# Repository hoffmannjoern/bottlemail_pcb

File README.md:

bottlemail_pcb
==============

PCB layout and schematics for Bottl(e)mail

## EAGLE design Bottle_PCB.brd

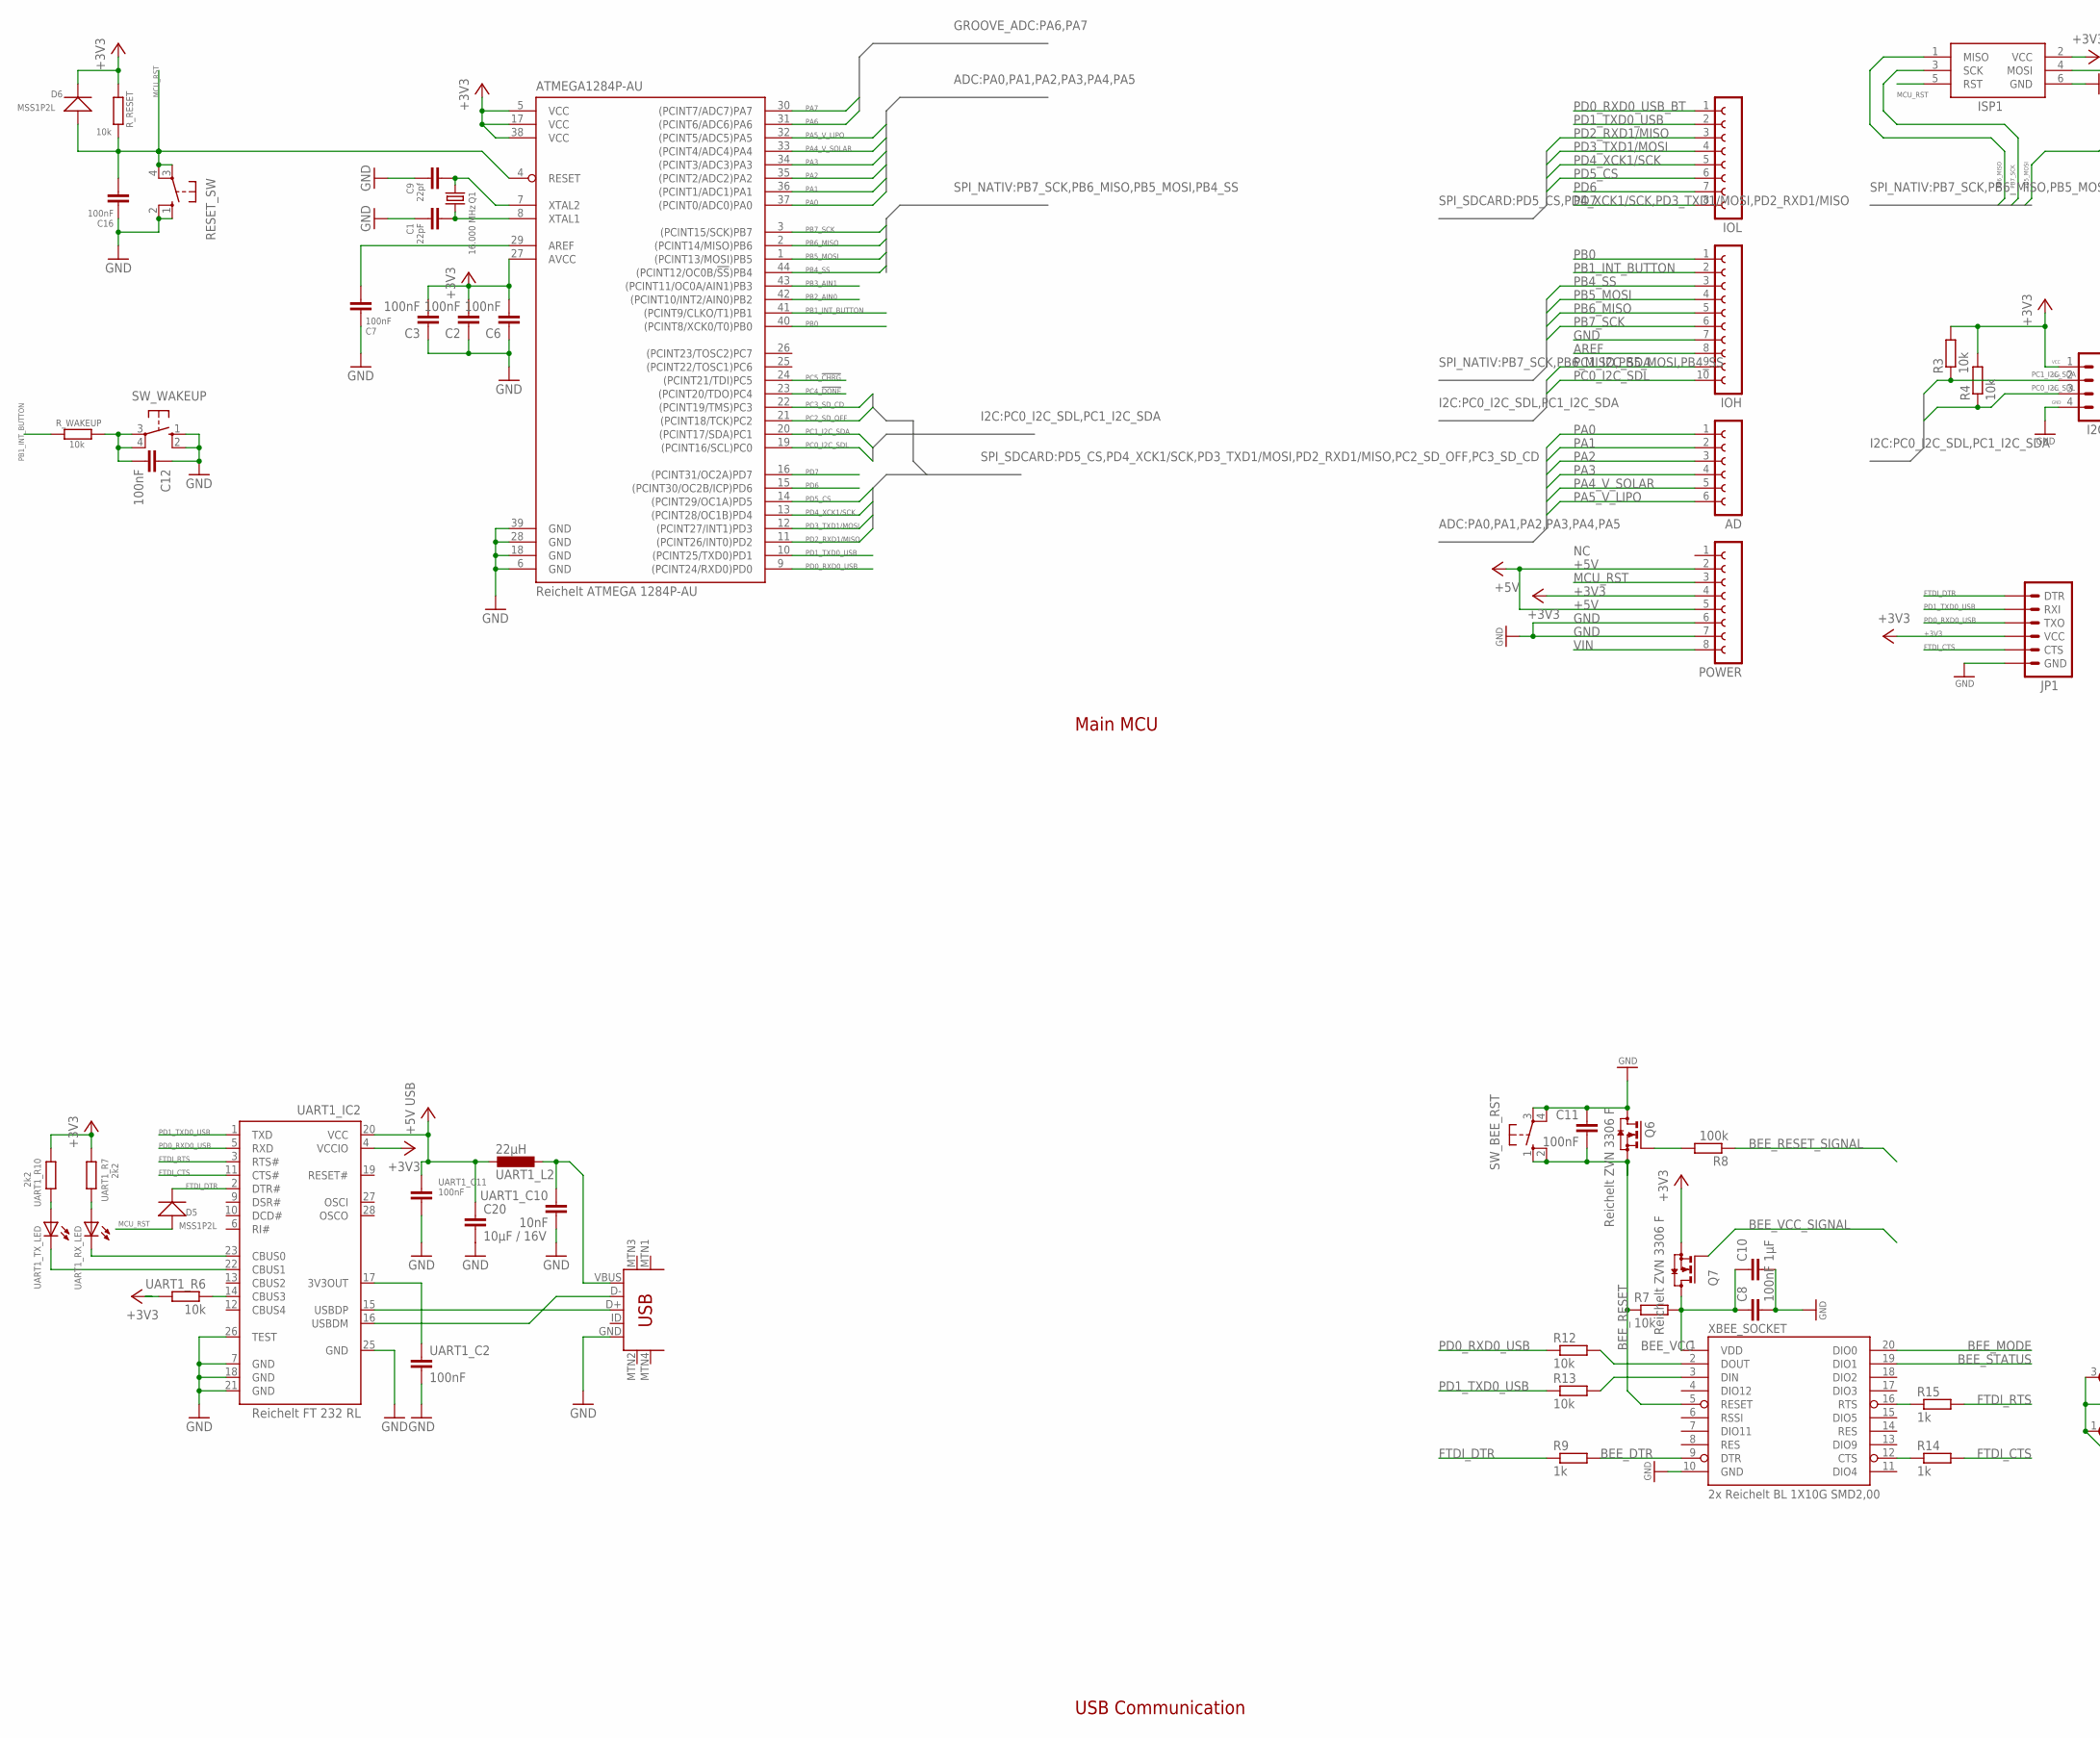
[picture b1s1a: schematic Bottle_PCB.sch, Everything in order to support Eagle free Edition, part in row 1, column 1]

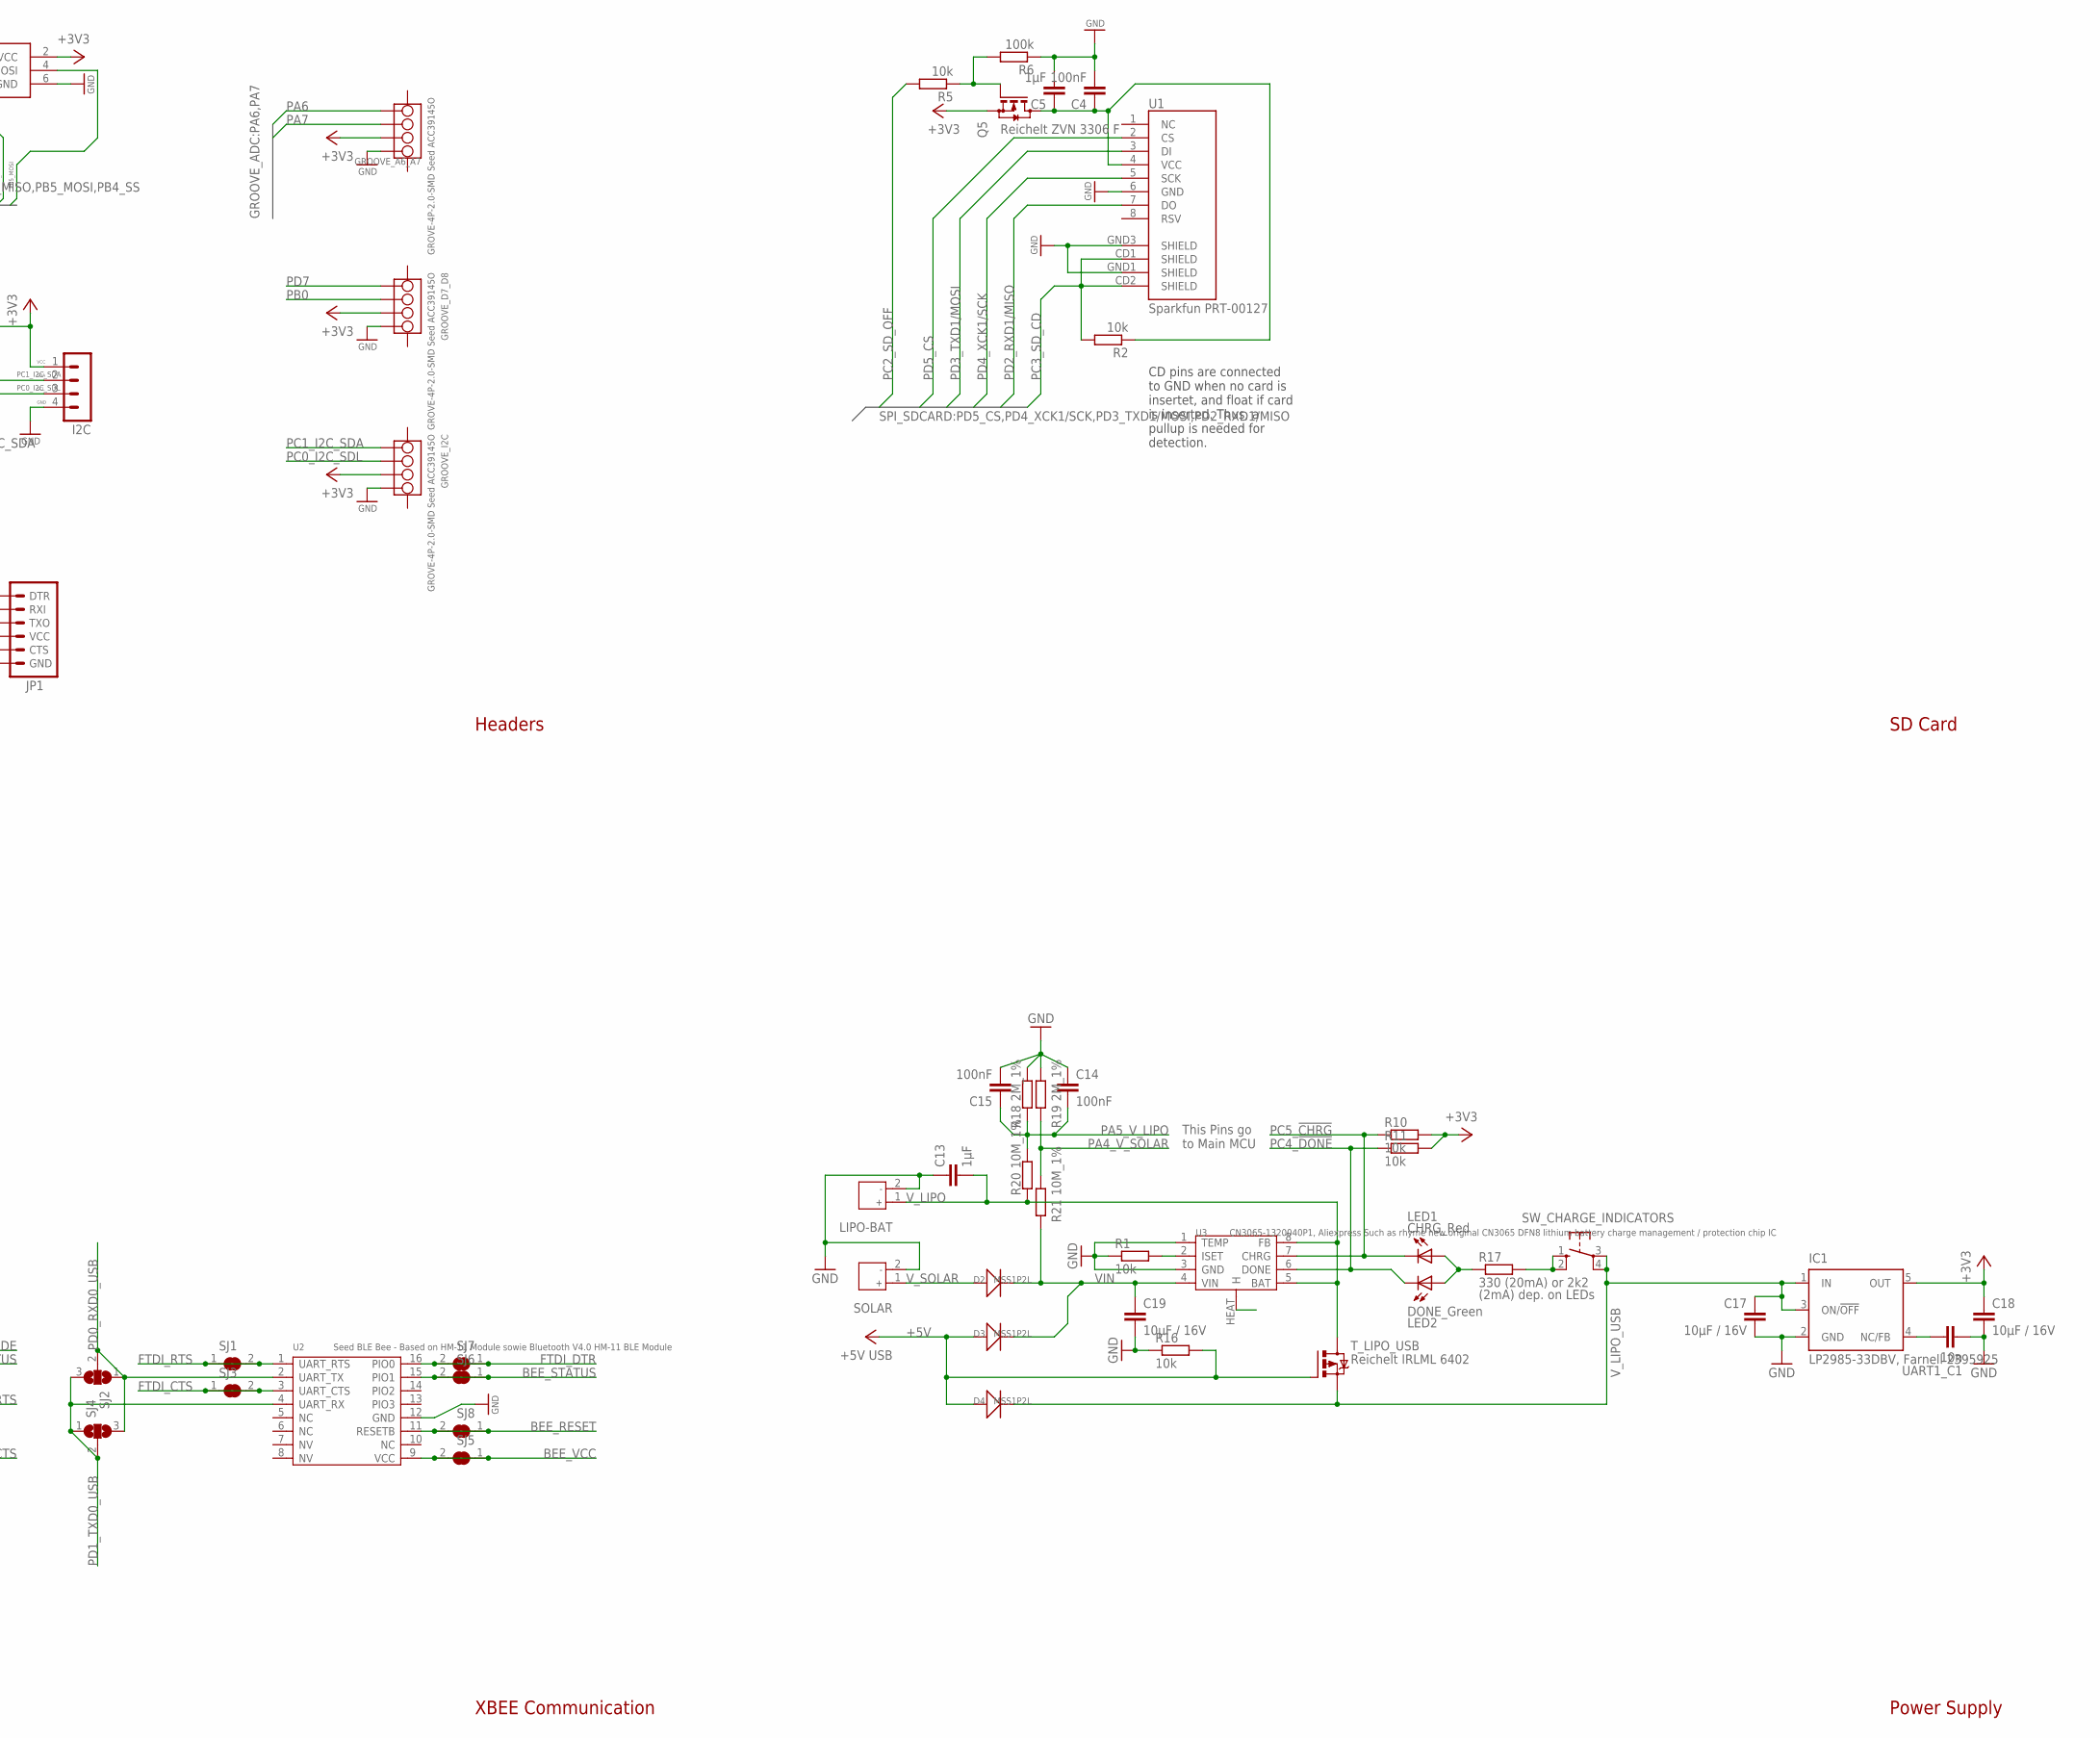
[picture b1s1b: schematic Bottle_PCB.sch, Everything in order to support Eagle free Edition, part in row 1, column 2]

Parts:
AD: FE06-1; FE06
ATMEGA1284P-AU: Reichelt ATMEGA 1284P-AU; TQFP44
C1: 22pF; C0603-ROUND
C2, C3, C4, C6, C7, C8, C11, C12, C14, C15, C16: 100nF; C0603-ROUND
C5, C10, C13: 1µF; C1210
C9: 22pf; C0603-ROUND
C17, C18, C19, C20: 10µF / 16V; C0805
D2, D3, D4, D5, D6: MSS1P2L; D1005
GROOVE_A6_A7: GROVE-4P-2.0-SMD Seed ACC39145O; 4P-SMD-2.0
GROOVE_D7_D8: GROVE-4P-2.0-SMD Seed ACC39145O; 4P-SMD-2.0
GROOVE_I2C: GROVE-4P-2.0-SMD Seed ACC39145O; 4P-SMD-2.0
I2C: MA04-1
IC1: LP2985-33DBV, Farnell 2395925; SOT23-DBV
IOH: FE10-1; FE10
IOL: FE08-1; FE08
ISP1: Reichelt WSL 6G; AVRISP
JP1: ARDUINO_SERIAL_PROGRAMPTH; 1X06
LED1: CHRG_Red; CHIPLED_0603
LED2: DONE_Green; CHIPLED_0603
LIPO-BAT: JACK-JST-2P-PW2.0; JST-2.0
POWER: FE08-1; FE08
Q1: 16.000 MHz; HC49U-V
Q5, Q6, Q7: Reichelt ZVN 3306 F; SOT23
R1, R2, R3, R4, R5, R7, R10, R11, R12, R13, R16: 10k; R0603-ROUND
R6, R8: 100k; R0603-ROUND
R9, R14, R15: 1k; R0603-ROUND
R17: 330 (20mA) or 2k2; R0603-ROUND
R18, R19: 2M_1%; R0603-ROUND
R20, R21: 10M_1%; R0603-ROUND
RESET_SW: 10-XX; B3F-10XX
R_RESET: 10k; R0603-ROUND
R_WAKEUP: 10k; R0603-ROUND
SJ1, SJ3, SJ5, SJ6, SJ7, SJ8: SJ
SJ2, SJ4: SJ2W; SJ_2
SOLAR: JACK-JST-2P-PW2.0; JST-2.0
SW_BEE_RST: 10-XX; B3F-10XX
SW_CHARGE_INDICATORS: 10-XX; B3F-10XX
SW_WAKEUP: 10-XX; B3F-10XX
T_LIPO_USB: Reichelt IRLML 6402; SOT23
U1: Sparkfun PRT-00127; MICRO-SD-SOCKET-PP
U2: Seed BLE Bee - Based on HM-11 Module sowie Blueto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; 16P-18.5X13.5X0.8
U3: CN3065-1320040P1, Aliexpress Such as rhyme new or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; DFN8
UART1_C1: 10n; C0603-ROUND
UART1_C2, UART1_C11: 100nF; C0603-ROUND
UART1_C10: 10nF; C0603-ROUND
UART1_IC2: Reichelt FT 232 RL; SSOP28
UART1_L2: 22µH; L1812
UART1_R6: 10k; R0603-ROUND
UART1_R7, UART1_R10: 2k2; R0603-ROUND
UART1_RX_LED, UART1_TX_LED: LEDCHIPLED_0603; CHIPLED_0603
USB_CONNECTOR: USB-MINIB-5PIN Sparkfun PRT-00587; USB-MINIB
XBEE_SOCKET: 2x Reichelt BL 1X10G SMD2,00; XBEE-SMD

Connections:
+3V3: ATMEGA1284P-AU.5 (VCC), ATMEGA1284P-AU.17 (VCC), ATMEGA1284P-AU.27 (AVCC), ATMEGA1284P-AU.38 (VCC), C2.2, C3.2, C6.2, C18.1, D6.-, GROOVE_A6_A7.2, GROOVE_D7_D8.2, GROOVE_I2C.2, I2C.1, IC1.5 (OUT), ISP1.2 (VCC), JP1.VCC, POWER.4, Q5.2 (S), Q7.2 (S), R3.2, R4.2, R10.2, R11.2, R_RESET.2, UART1_IC2.4 (VCCIO), UART1_R6.2, UART1_R7.1, UART1_R10.1
+5V: C20.1, D3.+, D4.+, POWER.2, POWER.5, R16.2, T_LIPO_USB.1 (G), UART1_C11.1, UART1_IC2.20 (VCC), UART1_L2.2
AREF: ATMEGA1284P-AU.29 (AREF), C7.2, IOH.8
BEE_DTR: R9.2, XBEE_SOCKET.9 (DTR)
BEE_MODE: XBEE_SOCKET.20 (DIO0)
BEE_RESET: C11.2, Q6.2 (S), R7.1, SJ8.1, SJ8.2, SW_BEE_RST.1 (S), SW_BEE_RST.2 (S1), U2.11 (RESETB), XBEE_SOCKET.5 (RESET)
BEE_RESET_SIGNAL: R8.1
BEE_STATUS: SJ6.1, SJ6.2, U2.15 (PIO1), XBEE_SOCKET.19 (DIO1)
BEE_VCC: C8.1, C10.1, Q7.3 (D), R7.2, SJ5.1, SJ5.2, U2.9 (VCC), XBEE_SOCKET.1 (VDD)
BEE_VCC_SIGNAL: Q7.1 (G)
FTDI_CTS: JP1.CTS, R14.2, SJ3.1, SJ3.2, U2.3 (UART_CTS), UART1_IC2.11 (CTS#)
FTDI_DTR: D5.-, JP1.DTR, R9.1, SJ7.1, SJ7.2, U2.16 (PIO0), UART1_IC2.2 (DTR#)
FTDI_RTS: R15.2, SJ1.1, SJ1.2, U2.1 (UART_RTS), UART1_IC2.3 (RTS#)
GND: ATMEGA1284P-AU.6 (GND), ATMEGA1284P-AU.18 (GND), ATMEGA1284P-AU.28 (GND), ATMEGA1284P-AU.39 (GND), C1.1, C2.1, C3.1, C4.2, C5.2, C6.1, C7.1, C8.2, C9.1, C10.2, C11.1, C12.1, C13.1, C14.1, C15.2, C16.1, C17.2, C18.2, C19.2, C20.2, GROOVE_A6_A7.1, GROOVE_D7_D8.1, GROOVE_I2C.1, I2C.4, IC1.2 (GND), IOH.7, ISP1.6 (GND), JP1.GND, LIPO-BAT.2, POWER.6, POWER.7, Q6.3 (D), R1.1, R6.1, R16.1, R18.2, R19.2, RESET_SW.1 (S), RESET_SW.2 (S1), SOLAR.2, SW_BEE_RST.3, SW_BEE_RST.4 (P1), SW_WAKEUP.1 (S), SW_WAKEUP.2 (S1), U1.6 (GND), U1.GND1 (SHIELD), U1.GND3 (SHIELD), U2.12 (GND), U3.1 (TEMP), U3.3 (GND), UART1_C1.2, UART1_C2.2, UART1_C10.2, UART1_C11.2, UART1_IC2.7 (GND), UART1_IC2.18 (GND), UART1_IC2.21 (GND), UART1_IC2.25 (GND), UART1_IC2.26 (TEST), USB_CONNECTOR.GND, XBEE_SOCKET.10 (GND)
MCU_RST: ATMEGA1284P-AU.4 (RESET), C16.2, D5.+, D6.+, ISP1.5 (RST), POWER.3, RESET_SW.3, RESET_SW.4 (P1), R_RESET.1
unnamed: UART1_R10.2, UART1_TX_LED.A
unnamed: UART1_C2.1, UART1_IC2.17 (3V3OUT)
unnamed: IC1.4 (NC/FB), UART1_C1.1
unnamed: UART1_IC2.16 (USBDM), USB_CONNECTOR.D-
unnamed: R14.1, XBEE_SOCKET.12 (CTS)
unnamed: R15.1, XBEE_SOCKET.16 (RTS)
unnamed: R12.2, XBEE_SOCKET.2 (DOUT)
unnamed: UART1_R7.2, UART1_RX_LED.A
unnamed: UART1_IC2.15 (USBDP), USB_CONNECTOR.D+
unnamed: UART1_IC2.14 (CBUS3), UART1_R6.1
unnamed: UART1_C10.1, UART1_L2.1, USB_CONNECTOR.VBUS
unnamed: UART1_IC2.23 (CBUS0), UART1_RX_LED.C
unnamed: UART1_IC2.22 (CBUS1), UART1_TX_LED.C
unnamed: R13.2, XBEE_SOCKET.3 (DIN)
unnamed: C12.2, R_WAKEUP.1, SW_WAKEUP.3, SW_WAKEUP.4 (P1)
unnamed: LED1.A, LED2.A, R17.1
unnamed: R17.2, SW_CHARGE_INDICATORS.1 (S), SW_CHARGE_INDICATORS.2 (S1)
unnamed: R1.2, U3.2 (ISET)
unnamed: C4.1, C5.1, Q5.3 (D), R2.1, U1.4 (VCC)
unnamed: Q5.1 (G), R5.1, R6.2
unnamed: Q6.1 (G), R8.2
PA0: AD.1, ATMEGA1284P-AU.37 ((PCINT0/ADC0)PA0)
PA1: AD.2, ATMEGA1284P-AU.36 ((PCINT1/ADC1)PA1)
PA2: AD.3, ATMEGA1284P-AU.35 ((PCINT2/ADC2)PA2)
PA3: AD.4, ATMEGA1284P-AU.34 ((PCINT3/ADC3)PA3)
PA4_V_SOLAR: AD.5, ATMEGA1284P-AU.33 ((PCINT4/ADC4)PA4), R19.1, R21.2
PA5_V_LIPO: AD.6, ATMEGA1284P-AU.32 ((PCINT5/ADC5)PA5), C14.2, C15.1, R18.1, R20.2
PA6: ATMEGA1284P-AU.31 ((PCINT6/ADC6)PA6), GROOVE_A6_A7.4
PA7: ATMEGA1284P-AU.30 ((PCINT7/ADC7)PA7), GROOVE_A6_A7.3
PB0: ATMEGA1284P-AU.40 ((PCINT8/XCK0/T0)PB0), GROOVE_D7_D8.3, IOH.1
PB1_INT_BUTTON: ATMEGA1284P-AU.41 ((PCINT9/CLKO/T1)PB1), IOH.2
PB2_AIN0: ATMEGA1284P-AU.42 ((PCINT10/INT2/AIN0)PB2)
PB3_AIN1: ATMEGA1284P-AU.43 ((PCINT11/OC0A/AIN1)PB3)
PB4_SS: ATMEGA1284P-AU.44 ((PCINT12/OC0B/!SS!)PB4), IOH.3
PB5_MOSI: ATMEGA1284P-AU.1 ((PCINT13/MOSI)PB5), IOH.4, ISP1.4 (MOSI)
PB6_MISO: ATMEGA1284P-AU.2 ((PCINT14/MISO)PB6), IOH.5, ISP1.1 (MISO)
PB7_SCK: ATMEGA1284P-AU.3 ((PCINT15/SCK)PB7), IOH.6, ISP1.3 (SCK)
PC0_I2C_SDL: ATMEGA1284P-AU.19 ((PCINT16/SCL)PC0), GROOVE_I2C.3, I2C.3, IOH.10, R4.1
PC1_I2C_SDA: ATMEGA1284P-AU.20 ((PCINT17/SDA)PC1), GROOVE_I2C.4, I2C.2, IOH.9, R3.1
PC2_SD_OFF: ATMEGA1284P-AU.21 ((PCINT18/TCK)PC2), R5.2
PC3_SD_CD: ATMEGA1284P-AU.22 ((PCINT19/TMS)PC3), R2.2, U1.CD1 (SHIELD), U1.CD2 (SHIELD)
PC4_!DONE: ATMEGA1284P-AU.23 ((PCINT20/TDO)PC4), LED2.C, R11.1, U3.6 (DONE)
PC5_!CHRG: ATMEGA1284P-AU.24 ((PCINT21/TDI)PC5), LED1.C, R10.1, U3.7 (CHRG)
PD0_RXD0_USB: ATMEGA1284P-AU.9 ((PCINT24/RXD0)PD0), JP1.TXO, R12.1, SJ2.1, SJ2.2, SJ4.3, U2.2 (UART_TX), UART1_IC2.5 (RXD)
PD0_RXD0_USB_BT: IOL.1
PD1_TXD0_USB: ATMEGA1284P-AU.10 ((PCINT25/TXD0)PD1), IOL.2, JP1.RXI, R13.1, SJ2.3, SJ4.1, SJ4.2, U2.4 (UART_RX), UART1_IC2.1 (TXD)
PD2_RXD1/MISO: ATMEGA1284P-AU.11 ((PCINT26/INT0)PD2), IOL.3, U1.7 (DO)
PD3_TXD1/MOSI: ATMEGA1284P-AU.12 ((PCINT27/INT1)PD3), IOL.4, U1.3 (DI)
PD4_XCK1/SCK: ATMEGA1284P-AU.13 ((PCINT28/OC1B)PD4), IOL.5, U1.5 (SCK)
PD5_CS: ATMEGA1284P-AU.14 ((PCINT29/OC1A)PD5), IOL.6, U1.2 (CS)
PD6: ATMEGA1284P-AU.15 ((PCINT30/OC2B/ICP)PD6), IOL.7
PD7: ATMEGA1284P-AU.16 ((PCINT31/OC2A)PD7), GROOVE_D7_D8.4, IOL.8
VIN: C19.1, D2.-, D3.-, POWER.8, R21.1, U3.4 (VIN)
V_LIPO: C13.2, LIPO-BAT.1, R20.1, T_LIPO_USB.2 (D), U3.5 (BAT), U3.8 (FB)
V_LIPO_USB: C17.1, D4.-, IC1.1 (IN), IC1.3 (ON/!OFF), SW_CHARGE_INDICATORS.3, SW_CHARGE_INDICATORS.4 (P1), T_LIPO_USB.3 (S)
V_SOLAR: D2.+, SOLAR.1
XTAL1: ATMEGA1284P-AU.8 (XTAL1), C1.2, Q1.1
XTAL2: ATMEGA1284P-AU.7 (XTAL2), C9.2, Q1.2

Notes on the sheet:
VCC
SDA
SCL
GND
Main MCU
Headers
XBEE Communication
USB Communication
SD Card
Power Supply
CD pins are connected to GND when no card is insertet, and float if card is inserted. Thus, a pullup is needed for detection.
(2mA) dep. on LEDs
This Pins go to Main MCU

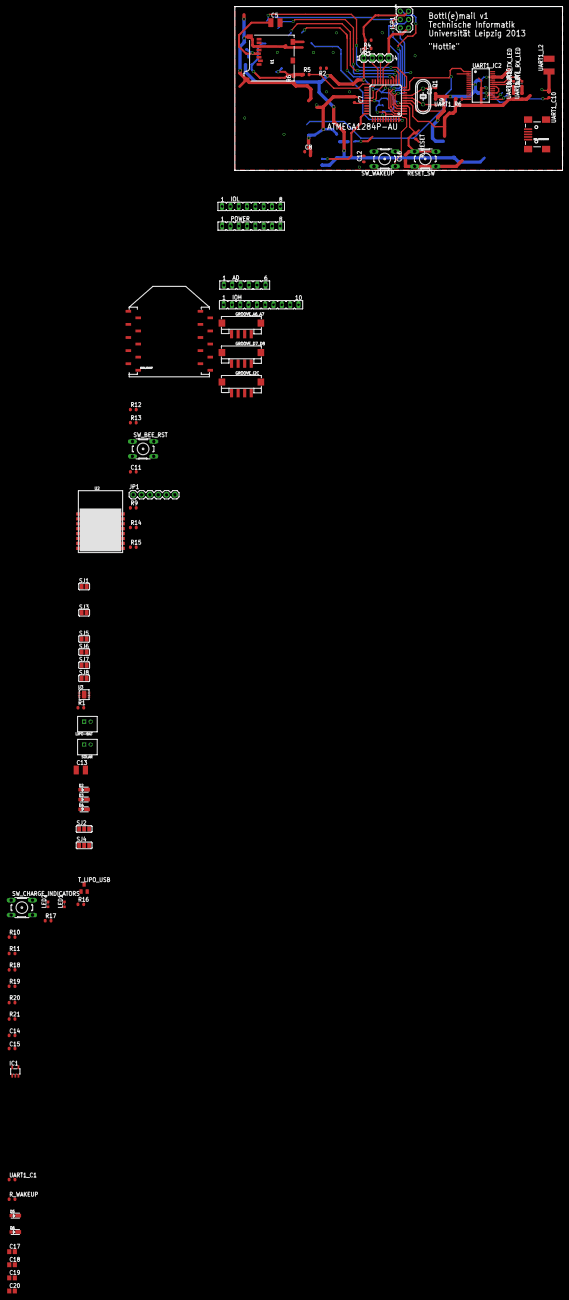
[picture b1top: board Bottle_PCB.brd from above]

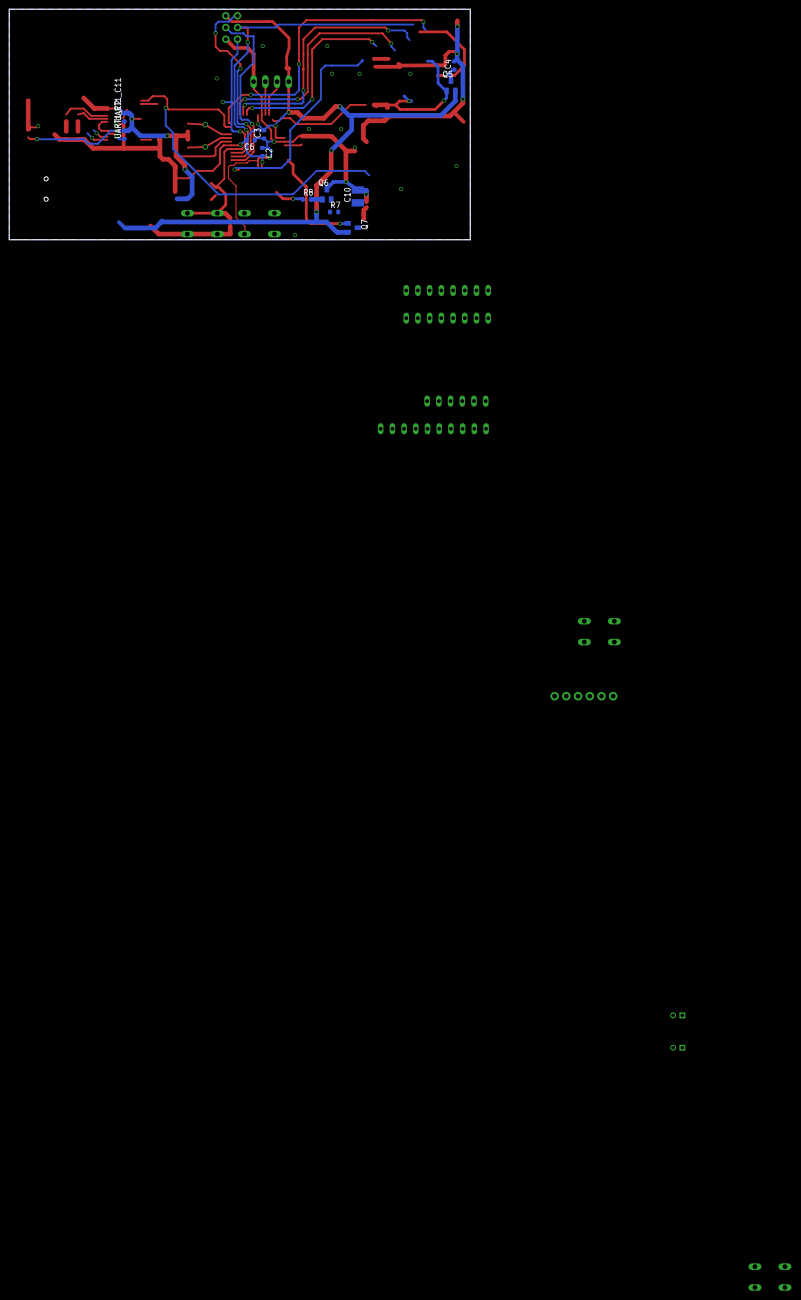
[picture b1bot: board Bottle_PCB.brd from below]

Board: 2 copper layers, 100.0 x 50.0 mm, 97 parts (12 on the bottom side), 67 nets.

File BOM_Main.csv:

Qty,Value,Device,Package,Parts,Description,MF,MPN,OC_FARNELL,OC_NEWARK,PROD_ID
4,,10-XX,B3F-10XX,"RESET_SW, SW_BEE_RST, SW_CHARGE_INDICATORS, SW_WAKEUP",OMRON SWITCH,,B3F-1000,176432,36M3542,
1,,ARDUINO_SERIAL_PROGRAMPTH,1X06,JP1,FTDI connector footprints,,,,,
1,,FE06-1,FE06,AD,FEMALE HEADER,,,unknown,unknown,
2,,FE08-1,FE08,"IOL, POWER",FEMALE HEADER,,,unknown,unknown,
1,,FE10-1,FE10,IOH,FEMALE HEADER,,,unknown,unknown,
2,,JACK-JST-2P-PW2.0,JST-2.0,"LIPO-BAT, SOLAR",,,,,,
2,,LEDCHIPLED_0603,CHIPLED_0603,"UART1_RX_LED, UART1_TX_LED",LED,,,,,
1,,MA04-1,MA04-1,I2C,PIN HEADER,,,unknown,unknown,
6,,SJ,SJ,"SJ1, SJ3, SJ5, SJ6, SJ7, SJ8",SMD solder JUMPER,,,,,
2,,SJ2W,SJ_2,"SJ2, SJ4",SMD solder JUMPER,,,,,
2,100k,R-EU_R0603,R0603-ROUND,"R6, R8","RESISTOR, European symbol",,,,,
10,100n,C-EUC0603,C0603-ROUND,"C2, C3, C4, C6, C7, C8, C11, C12, UART1_C2, UART1_C11","CAPACITOR, European symbol",,,,,
3,100nF,C-EUC0603,C0603-ROUND,"C14, C15, C16","CAPACITOR, European symbol",,,,,
2,10M_1%,R-EU_R0603,R0603-ROUND,"R20, R21","RESISTOR, European symbol",,,,,
14,10k,R-EU_R0603,R0603-ROUND,"R1, R2, R3, R4, R5, R7, R10, R11, R12, R13, R16, R_RESET, R_WAKEUP, UART1_R6","RESISTOR, European symbol",,,,,
2,10n,C-EUC0603,C0603-ROUND,"UART1_C1, UART1_C10","CAPACITOR, European symbol",,,,,
4,10µF / 16V,C-EUC0805,C0805,"C17, C18, C19, C20","CAPACITOR, European symbol",,,,,
1,16.000 MHz,CRYSTALHC49U-V,HC49U-V,Q1,CRYSTAL,,,1666969,unknown,
3,1k,R-EU_R0603,R0603-ROUND,"R9, R14, R15","RESISTOR, European symbol",,,,,
2,1µ,C-EUC1210,C1210,"C5, C10","CAPACITOR, European symbol",,,,,
1,1µF,C-EUC1210,C1210,C13,"CAPACITOR, European symbol",,,,,
2,22p,C-EUC0603,C0603-ROUND,"C1, C9","CAPACITOR, European symbol",,,,,
1,22µH,L-EUL1812,L1812,UART1_L2,"INDUCTOR, European symbol",,,,,
2,2M_1%,R-EU_R0603,R0603-ROUND,"R18, R19","RESISTOR, European symbol",,,,,
2,2k2,R-EU_R0603,R0603-ROUND,"UART1_R7, UART1_R10","RESISTOR, European symbol",,,,,
1,"2x Reichelt BL 1X10G SMD2,00",XBEE-1B3,XBEE-SMD,XBEE_SOCKET,Xbee module footprints,,,,,CONN-09042
1,330 (20mA) or 2k2,R-EU_R0603,R0603-ROUND,R17,"RESISTOR, European symbol",,,,,
1,CHRG_Red,LEDCHIPLED_0603,CHIPLED_0603,LED1,LED,,,,,
1,"CN3065-1320040P1, Aliexpress Such as rhyme new original CN3065 DFN8 lithium battery charge management / protection chip IC",CN3065-1320040P1,DFN8,U3,USB-Compatible Lithiumt-Ion Battery Charger with Thermal Regulation,,,,,
1,DONE_Green,LEDCHIPLED_0603,CHIPLED_0603,LED2,LED,,,,,
3,GROVE-4P-2.0-SMD Seed ACC39145O,GROVE-4P-2.0-SMD-FEMALE-REINFORCE-3470090P1,4P-SMD-2.0,"GROOVE_A6_A7, GROOVE_D7_D8, GROOVE_I2C",,,,,,
1,"LP2985-33DBV, Farnell 2395925",LP2985-XXDBVR33,SOT23-DBV,IC1,ULTRALOW-POWER 50-mA LOW-DROPOUT LINEAR REGULATORS,,,,,
5,MSS1P2U,D1005,D1005,"D2, D3, D4, D5, D6",,,,,,
1,Reichelt ATMEGA 1284P-AU,ATMEGA644A,TQFP44,ATMEGA1284P-AU,8-bit Microcontroller with 64K Bytes In-System Programmable Flash,,ATMEGA644PV-10AU,1455123,58M3748,
1,Reichelt FT 232 RL,FT232RL,SSOP28,UART1_IC2,Source: http://www.ftdichip.com/Documents/DataSheets/DS_FT232R_v104.pdf,,,,,
1,Reichelt IRLML 6402,MOS_P_SOT23_GDS,SOT23,T_LIPO_USB,P - CHANNEL ENHANCEMENT MODE (POWER ) MOS TRANSISTOR,,,,,
1,Reichelt WSL 6G,AVRISP-6,AVRISP,ISP1,AVR ISP HEADER,,,,,
3,Reichelt ZVN 3306 F,BSS123,SOT23,"Q5, Q6, Q7",N-CHANNEL MOS FET,,,,,
1,Seed BLE Bee - Based on HM-11 Module sowie Bluetooth V4.0 HM-11 BLE Module ,HM-11,16P-18.5X13.5X0.8,U2,Bluetooth Specification V4.0 BLE,,,,,
1,Sparkfun PRT-00127,USD-SOCKETNEW,MICRO-SD-SOCKET-PP,U1,microSD Socket,,,,,
1,USB-MINIB-5PIN Sparkfun PRT-00587,USB-MINIB-5PIN,USB-MINIB,USB_CONNECTOR,"Mini-USB ""B"" connector with 5th pin broken out.",,,,,

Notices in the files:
parts and their libraries:
SparkFun-Connectors: Licensing: CC v3.0 Share-Alike You are welcome to use this library for commercial purposes.
SparkFun-RF: Licensing: Creative Commons ShareAlike 4.0 International - https://creativecommons.org/licenses/by-sa/4.0
